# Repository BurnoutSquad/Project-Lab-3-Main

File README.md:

# Project-Lab-3 Team: Burnout Squad
Autonomous robot

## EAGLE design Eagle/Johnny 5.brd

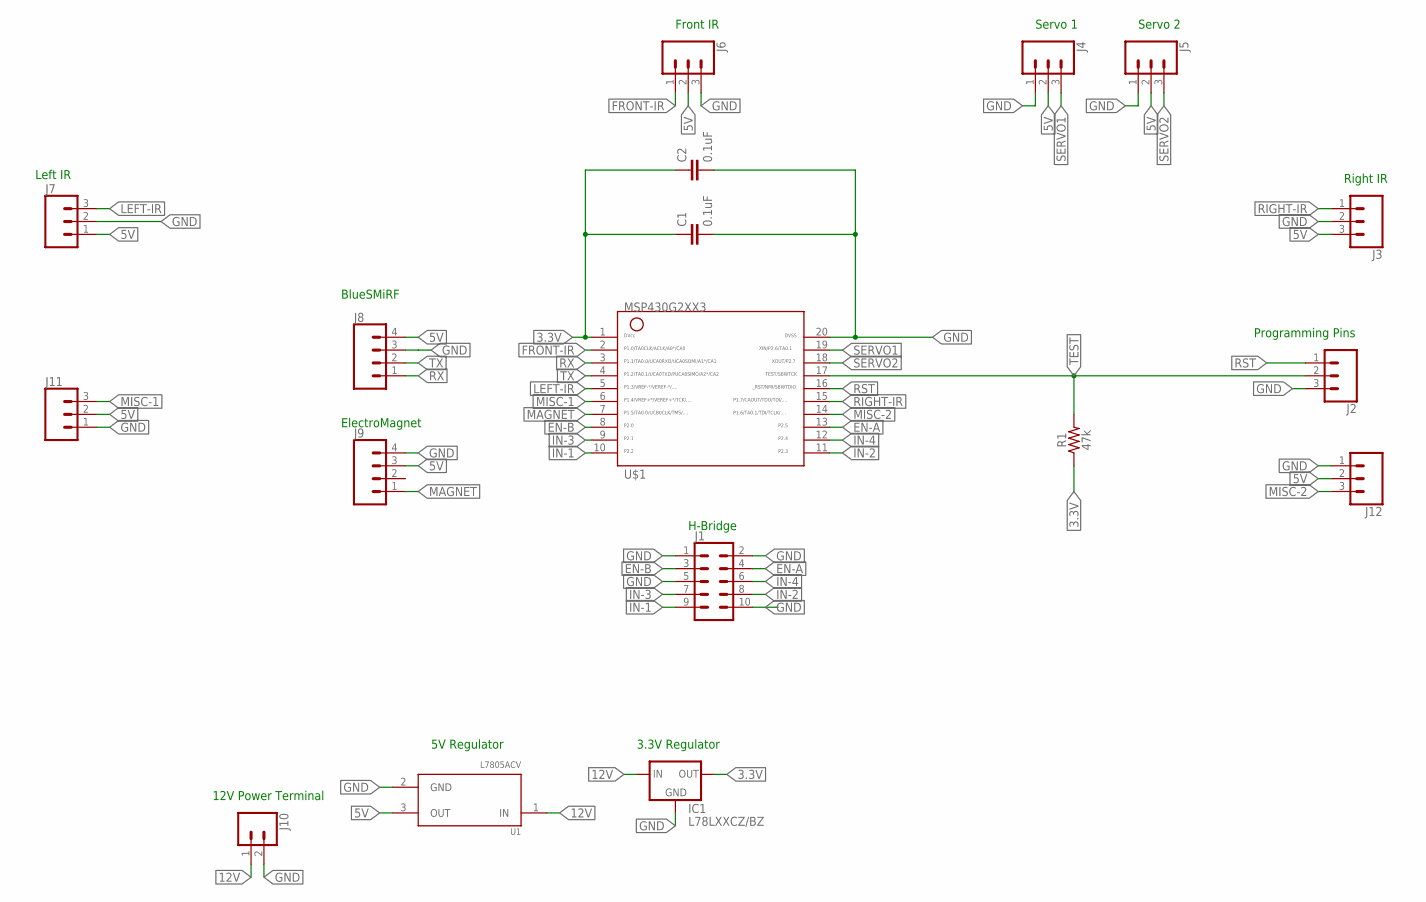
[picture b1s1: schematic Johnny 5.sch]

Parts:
C1, C2: 0.1uF; CAP-PTH-SMALL-KIT
IC1: L78LXXCZ/BZ; TO92
J1: CONN_05X2SHD; 2X5-SHROUDED
J2, J3, J4, J5, J6, J7, J11, J12: CONN_03; 1X03
J8, J9: CONN_04; 1X04
J10: CONN_025MM; SCREWTERMINAL-5MM-2
R1: 47k; 0603
U1: L7805ACV; TO254P460X1020X1945-3P
U$1: G2XX3---N20; N20

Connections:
3.3V: C1.1, C2.1, IC1.1 (OUT), R1.1, U$1.1
5V: J3.3, J4.2, J5.2, J6.2, J7.1, J8.4, J9.3, J11.2, J12.2, U1.3 (OUT)
12V: IC1.3 (IN), J10.1, U1.1 (IN)
EN-A: J1.4, U$1.13
EN-B: J1.3, U$1.8
FRONT-IR: J6.1, U$1.2
GND: C1.2, C2.2, IC1.2 (GND), J1.1, J1.2, J1.5, J1.10, J2.3, J3.2, J4.1, J5.1, J6.3, J7.2, J8.3, J9.4, J10.2, J11.1, J12.1, U1.2 (GND), U$1.20
IN-1: J1.9, U$1.10
IN-2: J1.8, U$1.11
IN-3: J1.7, U$1.9
IN-4: J1.6, U$1.12
LEFT-IR: J7.3, U$1.5
MAGNET: J9.1, U$1.7
MISC-1: J11.3, U$1.6
MISC-2: J12.3, U$1.14
RIGHT-IR: J3.1, U$1.15
RST: J2.1, U$1.16
RX: J8.1, U$1.3
SERVO1: J4.3, U$1.19
SERVO2: J5.3, U$1.18
TEST: J2.2, R1.2, U$1.17
TX: J8.2, U$1.4

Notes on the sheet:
H-Bridge
Programming Pins
Right IR
Left IR
Front IR
Servo 1
Servo 2
BlueSMiRF
ElectroMagnet
3.3V Regulator
12V Power Terminal
5V Regulator

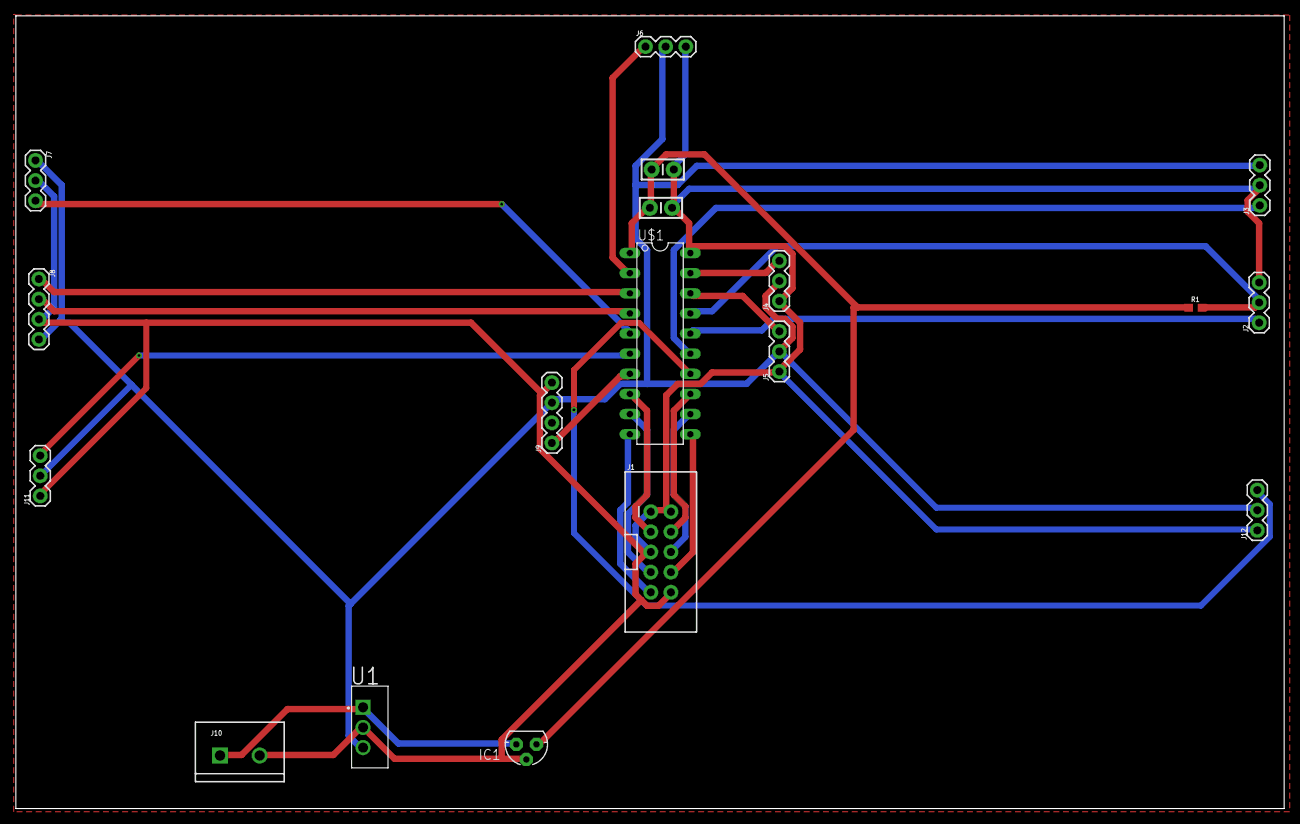
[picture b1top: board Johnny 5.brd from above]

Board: 2 copper layers, 160.0 x 100.0 mm, 18 parts (0 on the bottom side), 22 nets.

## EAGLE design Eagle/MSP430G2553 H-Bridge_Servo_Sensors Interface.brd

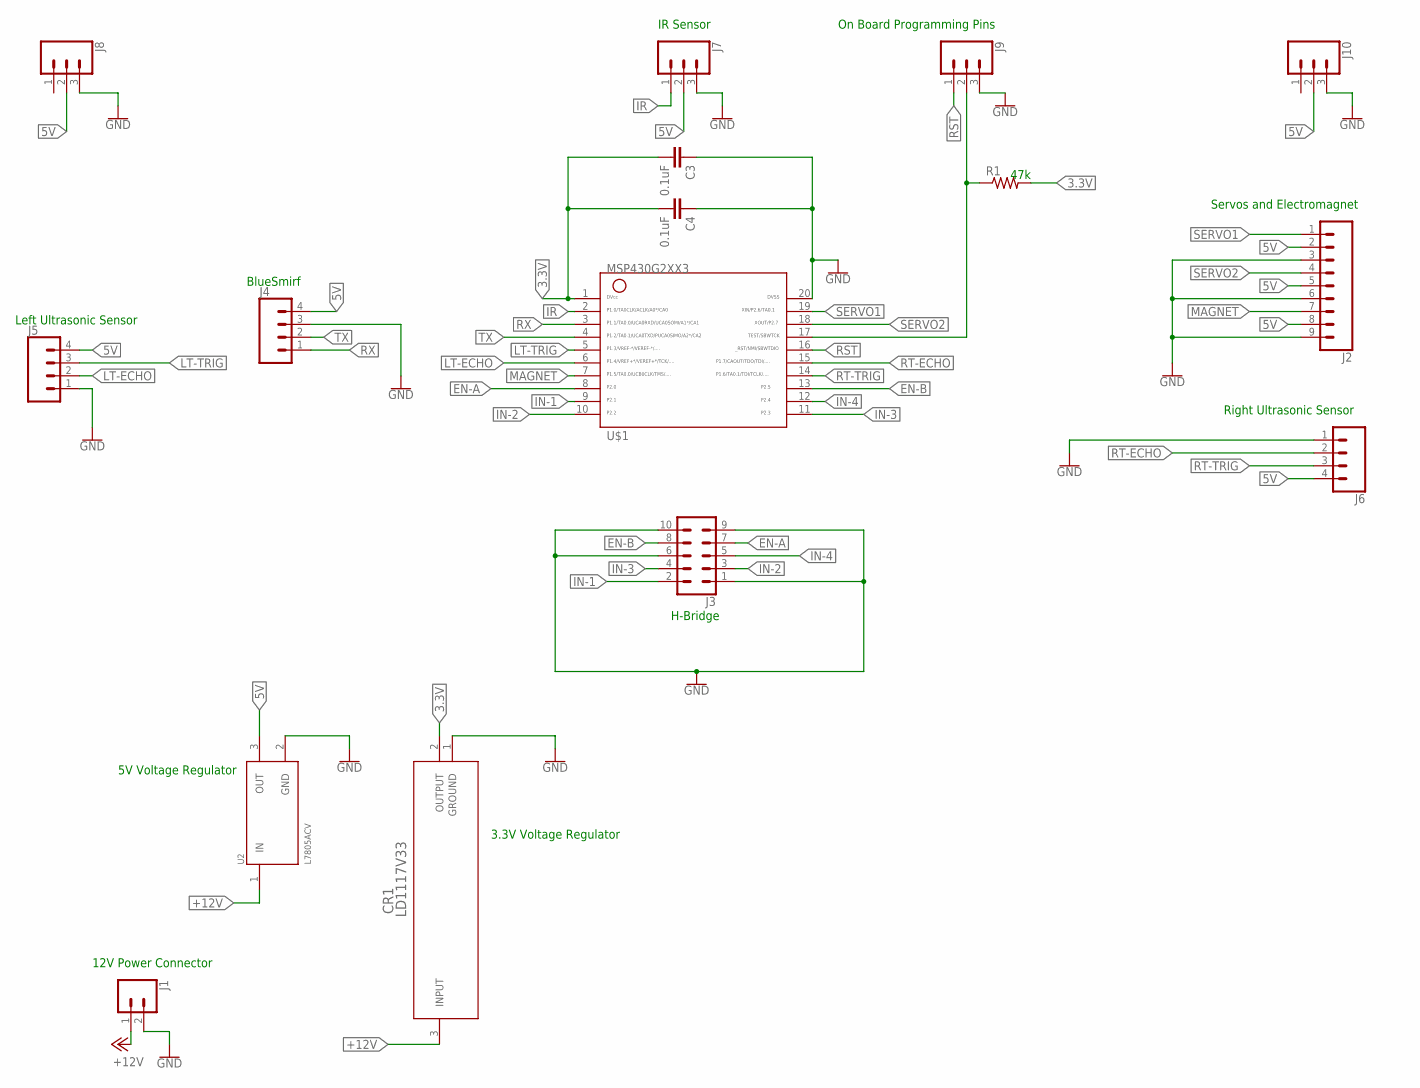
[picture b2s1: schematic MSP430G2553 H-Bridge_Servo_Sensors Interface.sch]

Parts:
C3, C4: 0.1uF; 0402
CR1: LD1117V33; TO-220
J1: CONN_023.5MM; SCREWTERMINAL-3.5MM-2
J2: CONN_09; 1X09
J3: CONN_05X2PTH; 2X5
J4, J5, J6: CONN_04; 1X04
J7, J8, J9, J10: CONN_03; 1X03
R1: R-US_R0201; R0201
U2: L7805ACV; TO254P460X1020X1945-3P
U$1: G2XX3---N20; N20

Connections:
3.3V: C3.2, C4.2, CR1.2 (OUTPUT), R1.2, U$1.1
5V: J2.2, J2.5, J2.8, J4.4, J5.4, J6.4, J7.2, J8.2, J10.2, U2.3 (OUT)
+12V: CR1.3 (INPUT), J1.1, U2.1 (IN)
EN-A: J3.7, U$1.8
EN-B: J3.8, U$1.13
GND: C3.1, C4.1, CR1.1 (GROUND), J1.2, J2.3, J2.6, J2.9, J3.1, J3.6, J3.9, J3.10, J4.3, J5.1, J6.1, J7.3, J8.3, J9.3, J10.3, U2.2 (GND), U$1.20
IN-1: J3.2, U$1.9
IN-2: J3.3, U$1.10
IN-3: J3.4, U$1.11
IN-4: J3.5, U$1.12
IR: J7.1, U$1.2
LT-ECHO: J5.2, U$1.6
LT-TRIG: J5.3, U$1.5
MAGNET: J2.7, U$1.7
unnamed: J9.2, R1.1, U$1.17
RST: J9.1, U$1.16
RT-ECHO: J6.2, U$1.15
RT-TRIG: J6.3, U$1.14
RX: J4.1, U$1.3
SERVO1: J2.1, U$1.19
SERVO2: J2.4, U$1.18
TX: J4.2, U$1.4

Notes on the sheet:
Left Ultrasonic Sensor
Right Ultrasonic Sensor
IR Sensor
5V Voltage Regulator
3.3V Voltage Regulator
12V Power Connector
Servos and Electromagnet
H-Bridge
BlueSmirf
On Board Programming Pins
47k

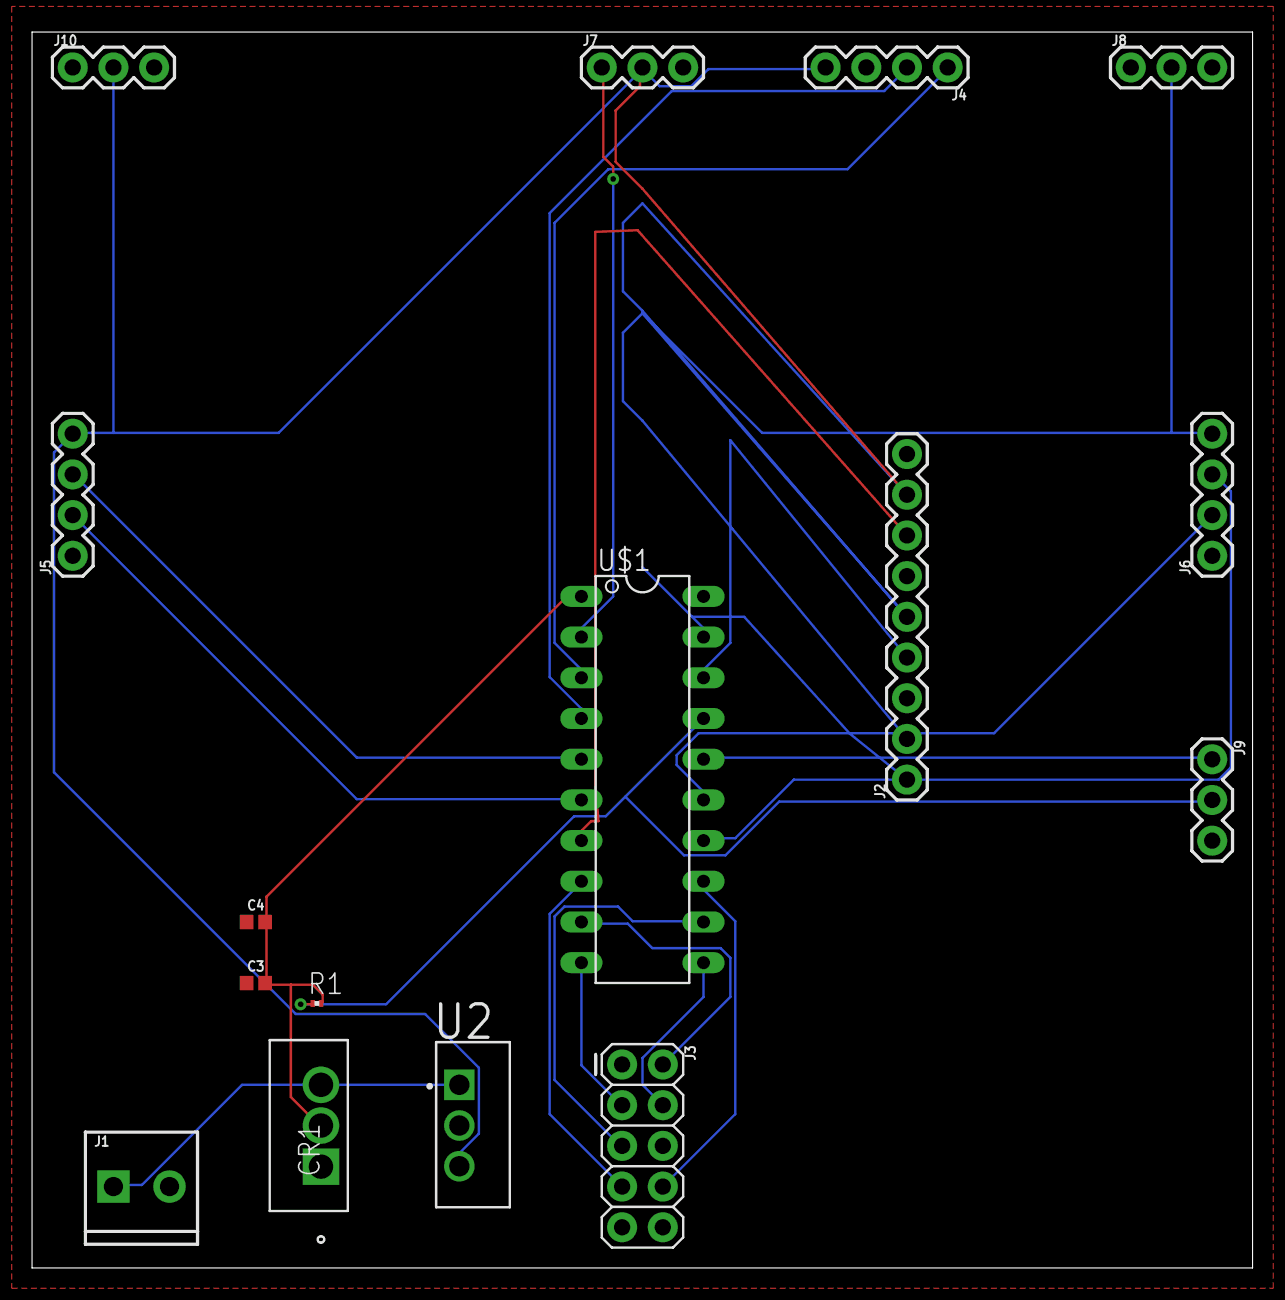
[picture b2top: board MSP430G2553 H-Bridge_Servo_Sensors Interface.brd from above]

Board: 2 copper layers, 76.2 x 77.1 mm, 16 parts (0 on the bottom side), 22 nets.

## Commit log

2018-02-12 Create Rover code with pb and 1 sensor
2018-02-12 Create Rover code with pb
2018-02-19 Create file
2018-02-19 Create n
2018-02-19 Rename Rover code with pb to Code/Rover code with pb
2018-02-19 Rename Rover code with pb and 1 sensor to Code/Rover code with pb and 1 sensor
2018-02-19 Rename Tank_Test.c to Tank_Prototype.c
2018-02-19 Initial Lab Notebook: Week 2
2018-02-19 Add files via upload
    System Diagram
2018-02-19 Rename Bluetooth_Brain.c to Code/Bluetooth_Brain.c
2018-03-07 Added System Flowchart
2018-03-07 Create Schematics and Drawings
2018-03-20 Add files via upload
    Eagle CAD Schematic and PCB
2018-03-22 Create Budget
2018-03-22 Uploaded MacBook side code
2018-04-04 Rename main.c to Robot_Arm.c
2018-04-12 Updated C++ code
    multiple changes including Blob detection code
2018-05-02 For UART Testing
2018-05-02 Fixed UART Test
2018-05-05 Create Demo Videos
2018-05-07 Create flowcharts
2018-05-11 Final code from Demo Day
2018-05-11 Rename ControlInterface.cpp to ControlInterfaceFinal.cpp
2018-05-11 Added sources file
2018-07-03 Rename Final Working Nav Code.txt to Final Working Nav Code.c

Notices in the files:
parts and their libraries:
SparkFun-Capacitors: Licensing: Creative Commons ShareAlike 4.0 International - https://creativecommons.org/licenses/by-sa/4.0
